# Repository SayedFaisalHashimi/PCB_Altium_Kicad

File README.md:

My PCB design Projects 
Note : Some Boards may not work I do not take the responsibilty.

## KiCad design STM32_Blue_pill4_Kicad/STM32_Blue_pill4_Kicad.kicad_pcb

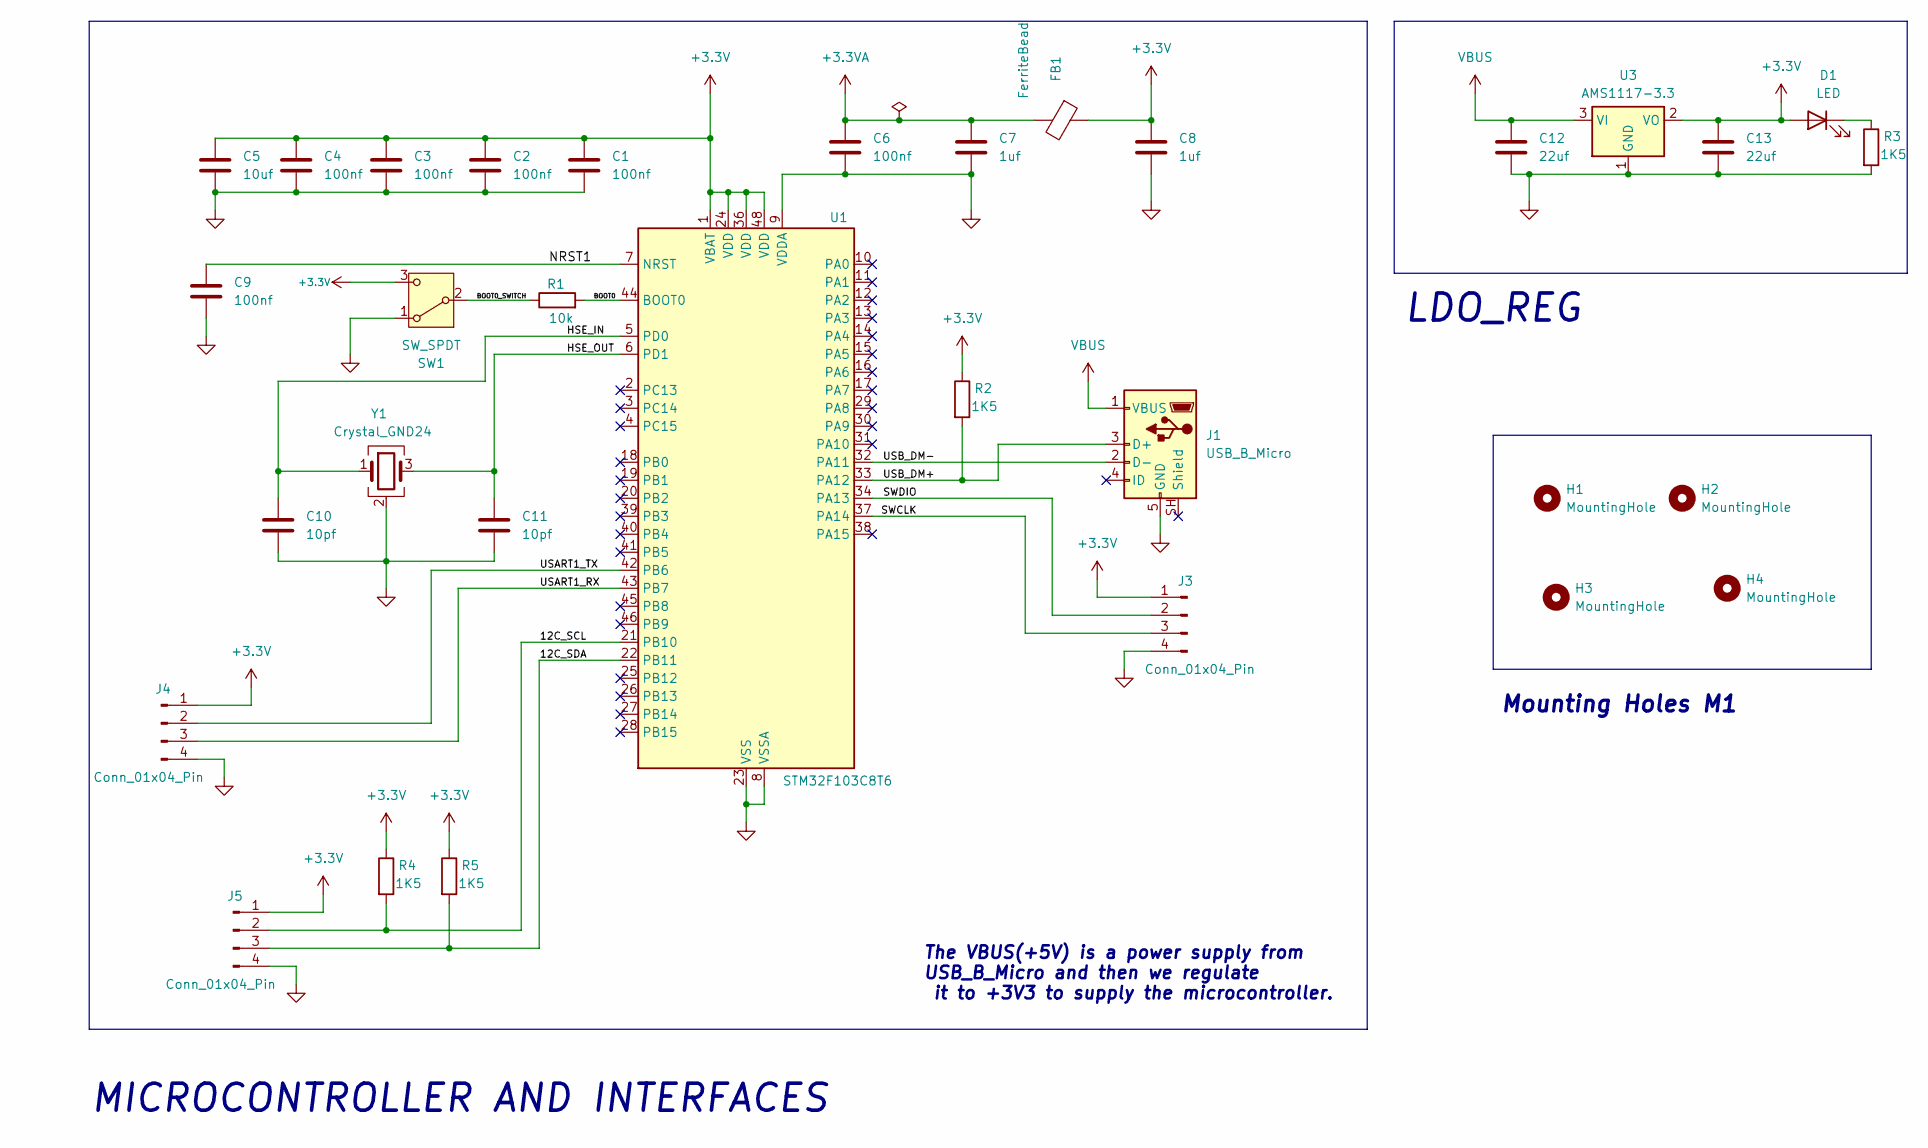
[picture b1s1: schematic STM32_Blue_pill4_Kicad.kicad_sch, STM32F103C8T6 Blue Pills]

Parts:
C1, C3, C4, C6, C9: 100nf; C_0402_1005Metric
C2: 100nf; C_0201_0603Metric
C5: 10uf; C_0603_1608Metric
C7, C8: 1uf; C_0402_1005Metric
C10, C11: 10pf; C_0402_1005Metric
C12, C13: 22uf; C_0805_2012Metric
D1: LED; LED_0603_1608Metric
FB1: FerriteBead; L_0603_1608Metric
H1, H2, H3, H4: MountingHole; MountingHole_2.2mm_M2
J1: USB_B_Micro; USB_Micro-B_Wuerth_629105150521
J3, J4, J5: Conn_01x04_Pin; PinHeader_1x04_P2.54mm_Vertical
R1: 10k; R_0402_1005Metric
R2, R3, R4, R5: 1K5; R_0402_1005Metric
SW1: SW_SPDT; SW_SPDT_PCM12
U1: STM32F103C8T6; LQFP-48_7x7mm_P0.5mm
U3: AMS1117-3.3; SOT-223-3_TabPin2
Y1: Crystal_GND24; Crystal_SMD_3225-4Pin_3.2x2.5mm

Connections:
+3.3V: C1.1, C2.1, C3.1, C4.1, C5.1, C8.1, C13.1, D1.2 (A), FB1.1, J3.1, J4.1, J5.1, R2.1, R4.1, R5.1, SW1.3 (C), U1.1 (VBAT), U1.24 (VDD), U1.36 (VDD), U1.48 (VDD), U3.2 (VO)
+3.3VA: C6.1, C7.1, FB1.2
/12C_SCL: J5.2, R4.2, U1.21 (PB10)
/12C_SDA: J5.3, R5.2, U1.22 (PB11)
/BOOT0: R1.2, U1.44 (BOOT0)
/BOOT0_SWITCH: R1.1, SW1.2 (B)
/HSE_IN: C10.1, U1.5 (PD0), Y1.1
/HSE_OUT: C11.1, U1.6 (PD1), Y1.3
/NRST1: C9.1, U1.7 (NRST)
/SWCLK: J3.3, U1.37 (PA14)
/SWDIO: J3.2, U1.34 (PA13)
/USART1_RX: J4.3, U1.43 (PB7)
/USART1_TX: J4.2, U1.42 (PB6)
/USB_DM+: J1.3 (D+), R2.2, U1.33 (PA12)
/USB_DM-: J1.2 (D-), U1.32 (PA11)
GND: C1.2, C2.2, C3.2, C4.2, C5.2, C6.2, C7.2, C8.2, C9.2, C10.2, C11.2, C12.2, C13.2, J1.5 (GND), J3.4, J4.4, J5.4, R3.2, SW1.1 (A), U1.8 (VSSA), U1.9 (VDDA), U1.23 (VSS), U1.35 (VSS), U1.47 (VSS), U3.1 (GND), Y1.2 (G), Y1.4 (G)
unnamed: D1.1 (K), R3.1
VBUS: C12.1, J1.1 (VBUS), U3.3 (VI)

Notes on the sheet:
LDO_REG
The VBUS(+5V) is a power supply from USB_B_Micro and then we regulate it to +3V3 to supply the microcontroller.
MICROCONTROLLER AND INTERFACES
Mounting Holes M1

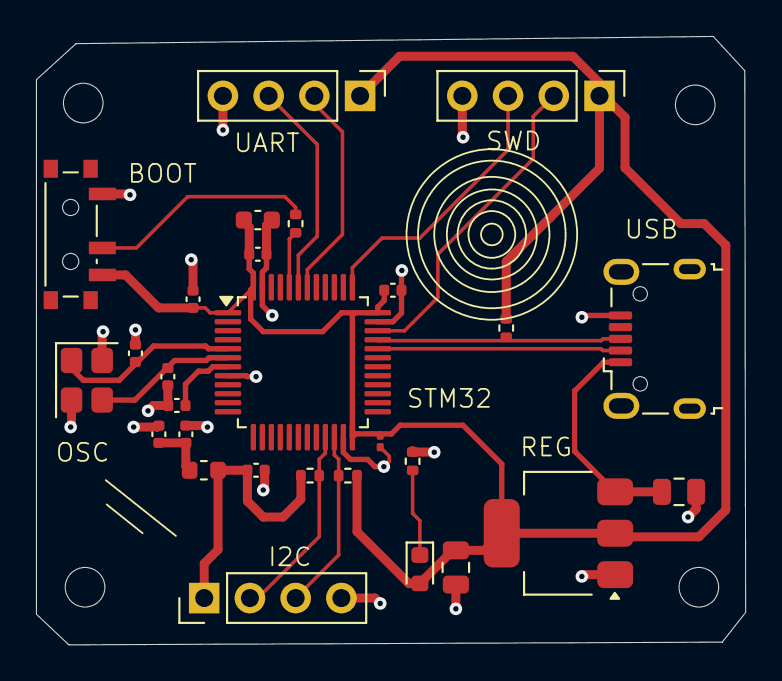
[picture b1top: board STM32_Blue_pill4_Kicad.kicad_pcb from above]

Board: 2 copper layers, 39.4 x 33.8 mm, 32 parts (0 on the bottom side), 18 nets.

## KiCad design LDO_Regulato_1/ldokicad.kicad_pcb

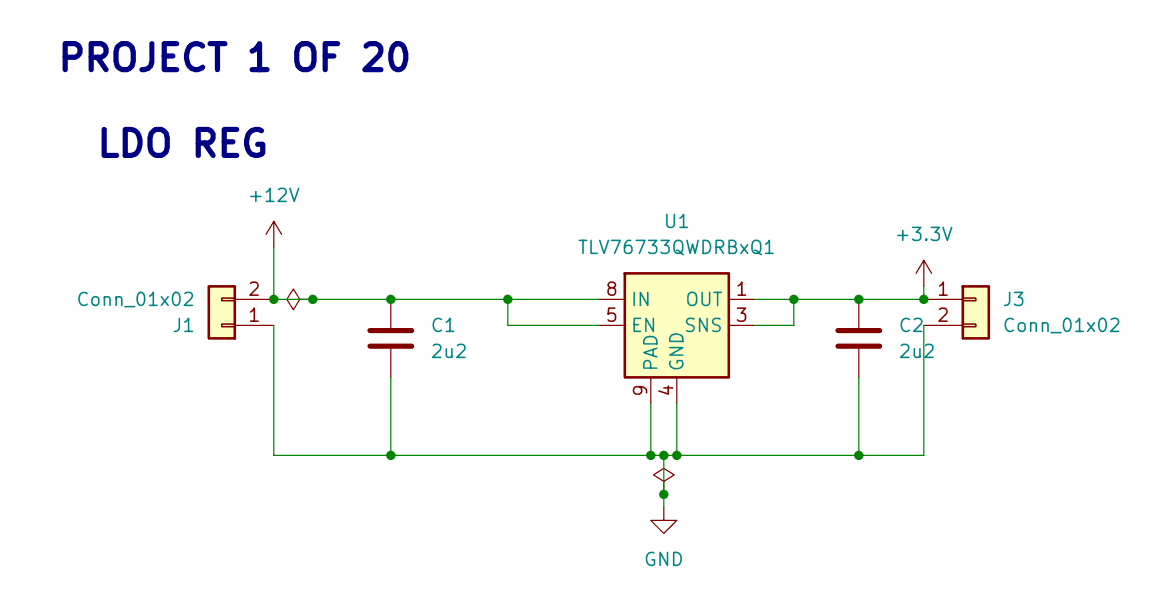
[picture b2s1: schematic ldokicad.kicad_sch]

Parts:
C1, C2: 2u2; C_0805_2012Metric
J1, J3: Conn_01x02; TerminalBlock_Phoenix_PT-1,5-2-5.0-H_1x02_P5.00mm_Horizontal
U1: TLV76733QWDRBxQ1; VSON-8-1EP_3x3mm_P0.65mm_EP1.65x2.4mm

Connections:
+3.3V: C2.1, J3.1, U1.1 (OUT), U1.3 (SNS)
+12V: C1.1, J1.2, U1.5 (EN), U1.8 (IN)
GND: C1.2, C2.2, J1.1, J3.2, U1.4 (GND), U1.6 (GND), U1.9 (PAD)

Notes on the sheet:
PROJECT 1 OF 20
LDO REG

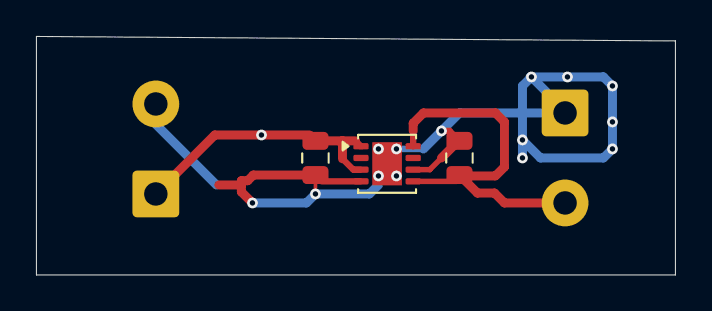
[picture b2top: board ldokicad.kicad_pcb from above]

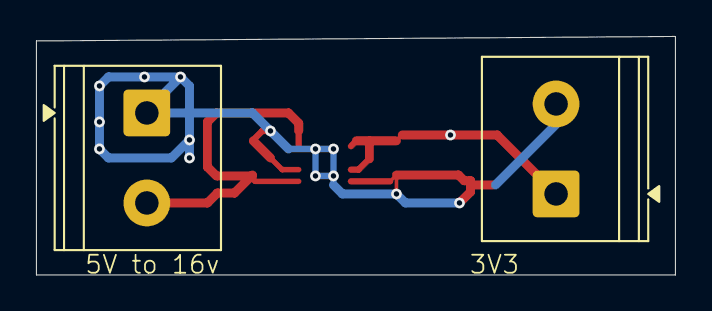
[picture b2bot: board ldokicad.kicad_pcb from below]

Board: 2 copper layers, 35.5 x 13.2 mm, 5 parts (2 on the bottom side), 3 nets.
